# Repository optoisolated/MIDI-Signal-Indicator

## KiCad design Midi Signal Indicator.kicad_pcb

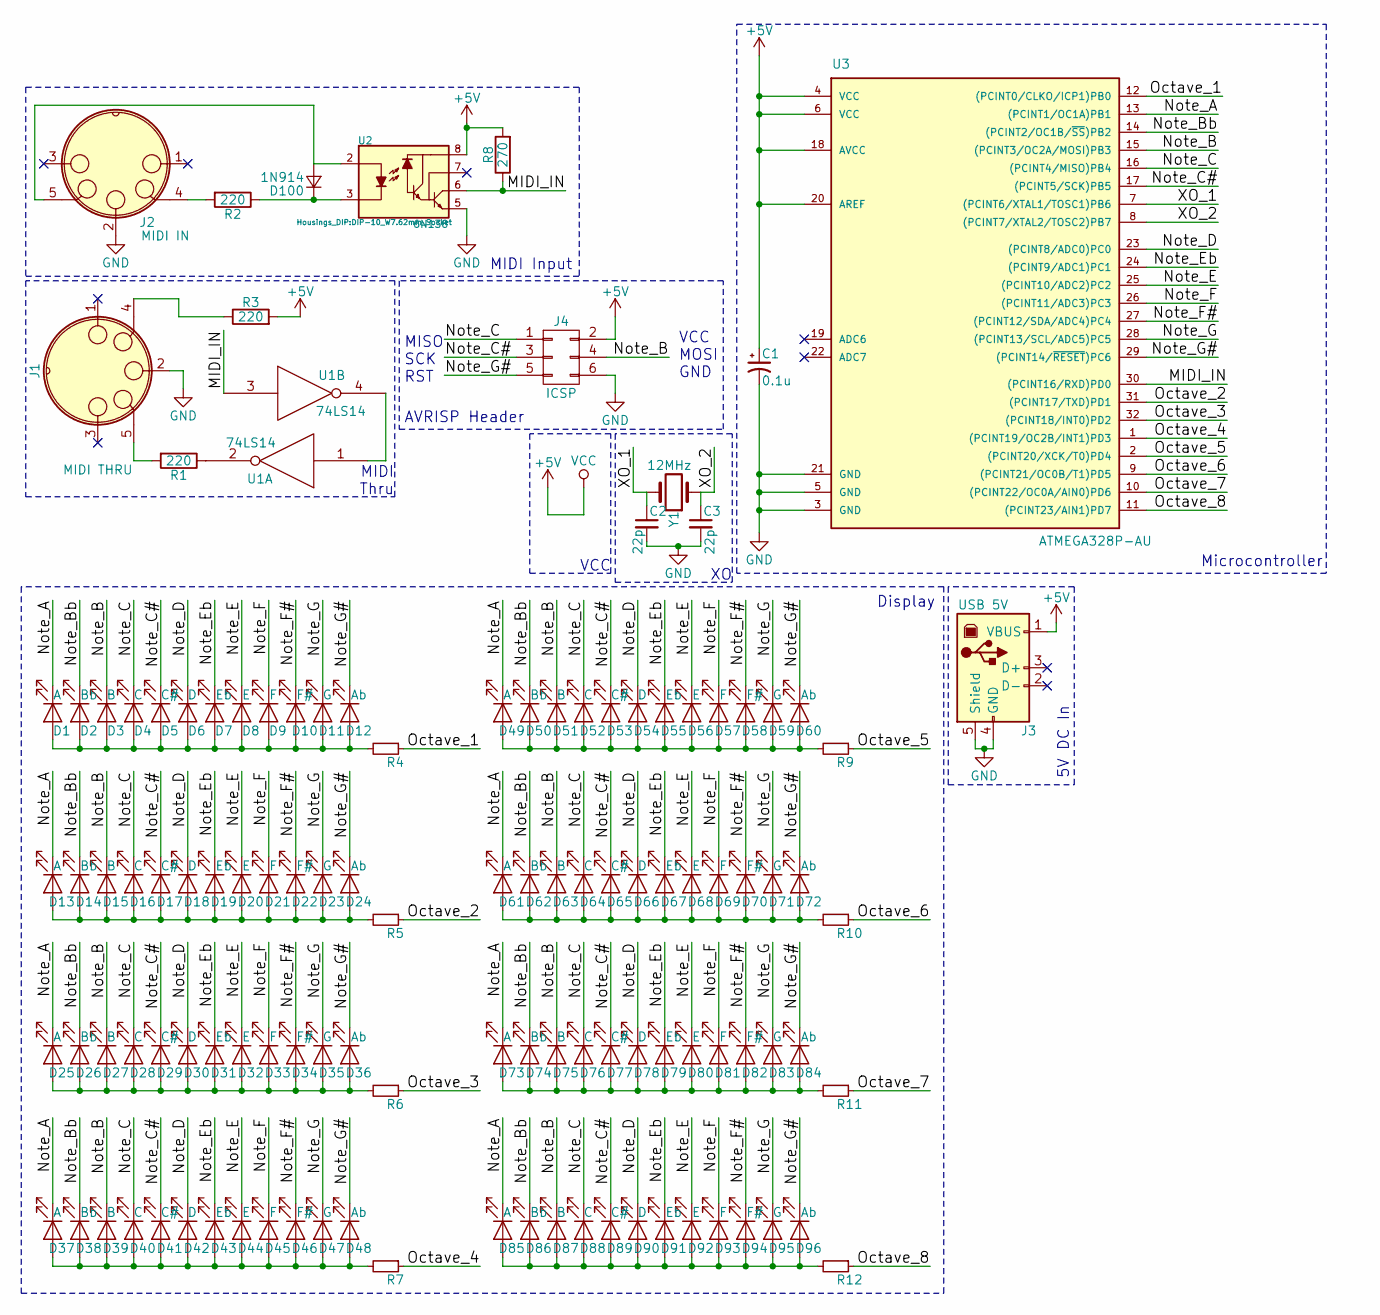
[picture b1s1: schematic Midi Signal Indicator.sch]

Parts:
C1: 0.1u; C_Disc_D5.0mm_W2.5mm_P2.50mm
C2, C3: 22p; C_Disc_D5.0mm_W2.5mm_P2.50mm
D1, D13, D25, D37, D49, D61, D73, D85: A; LED_1206
D2, D14, D26, D38, D50, D62, D74, D86: Bb; LED_1206
D3, D15, D27, D39, D51, D63, D75, D87: B; LED_1206
D4, D16, D28, D40, D52, D64, D76, D88: C; LED_1206
D5, D17, D29, D41, D53, D65, D77, D89: C#; LED_1206
D6, D18, D30, D42, D54, D66, D78, D90: D; LED_1206
D7, D19, D31, D43, D55, D67, D79, D91: Eb; LED_1206
D8, D20, D32, D44, D56, D68, D80, D92: E; LED_1206
D9, D21, D33, D45, D57, D69, D81, D93: F; LED_1206
D10, D22, D34, D46, D58, D70, D82, D94: F#; LED_1206
D11, D23, D35, D47, D59, D71, D83, D95: G; LED_1206
D12, D24, D36, D48, D60, D72, D84, D96: Ab; LED_1206
D100: 1N914; D_DO-15_P12.70mm_Horizontal
J1: MIDI THRU; SDS-50J
J2: MIDI IN; SDS-50J
J3: USB 5V; USB_B
J4: ICSP; Pin_Header_Straight_2x03_Pitch2.54mm
R1, R2, R3, R4, R5, R6, R7, R9, R10, R11, R12: 220; R_0603
R8: 270; R_0603
U1: 74LS14; DIP-14_W7.62mm_Socket
U2: 6N138; DIP-10_W7.62mm_Socket
U3: ATMEGA328P-AU; DIP-32_W7.62mm
Y1: 12MHz; Crystal_HC52-U_Vertical

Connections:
+5V: C1.1, J3.1 (VBUS), J4.2, R3.2, R8.2, U1.14 (VCC), U2.8, U3.4 (VCC), U3.6 (VCC), U3.18 (AVCC), U3.20 (AREF)
/MIDI_IN: R8.1, U1.3, U2.6, U3.30 ((PCINT16/RXD)PD0)
/Note_A: D1.1 (K), D13.1 (K), D25.1 (K), D37.1 (K), D49.1 (K), D61.1 (K), D73.1 (K), D85.1 (K), U3.13 ((PCINT1/OC1A)PB1)
/Note_B: D3.1 (K), D15.1 (K), D27.1 (K), D39.1 (K), D51.1 (K), D63.1 (K), D75.1 (K), D87.1 (K), J4.4, U3.15 ((PCINT3/OC2A/MOSI)PB3)
/Note_Bb: D2.1 (K), D14.1 (K), D26.1 (K), D38.1 (K), D50.1 (K), D62.1 (K), D74.1 (K), D86.1 (K), U3.14 ((PCINT2/OC1B/~SS~)PB2)
/Note_C: D4.1 (K), D16.1 (K), D28.1 (K), D40.1 (K), D52.1 (K), D64.1 (K), D76.1 (K), D88.1 (K), J4.1, U3.16 ((PCINT4/MISO)PB4)
/Note_C#: D5.1 (K), D17.1 (K), D29.1 (K), D41.1 (K), D53.1 (K), D65.1 (K), D77.1 (K), D89.1 (K), J4.3, U3.17 ((PCINT5/SCK)PB5)
/Note_D: D6.1 (K), D18.1 (K), D30.1 (K), D42.1 (K), D54.1 (K), D66.1 (K), D78.1 (K), D90.1 (K), U3.23 ((PCINT8/ADC0)PC0)
/Note_E: D8.1 (K), D20.1 (K), D32.1 (K), D44.1 (K), D56.1 (K), D68.1 (K), D80.1 (K), D92.1 (K), U3.25 ((PCINT10/ADC2)PC2)
/Note_Eb: D7.1 (K), D19.1 (K), D31.1 (K), D43.1 (K), D55.1 (K), D67.1 (K), D79.1 (K), D91.1 (K), U3.24 ((PCINT9/ADC1)PC1)
/Note_F: D9.1 (K), D21.1 (K), D33.1 (K), D45.1 (K), D57.1 (K), D69.1 (K), D81.1 (K), D93.1 (K), U3.26 ((PCINT11/ADC3)PC3)
/Note_F#: D10.1 (K), D22.1 (K), D34.1 (K), D46.1 (K), D58.1 (K), D70.1 (K), D82.1 (K), D94.1 (K), U3.27 ((PCINT12/SDA/ADC4)PC4)
/Note_G: D11.1 (K), D23.1 (K), D35.1 (K), D47.1 (K), D59.1 (K), D71.1 (K), D83.1 (K), D95.1 (K), U3.28 ((PCINT13/SCL/ADC5)PC5)
/Note_G#: D12.1 (K), D24.1 (K), D36.1 (K), D48.1 (K), D60.1 (K), D72.1 (K), D84.1 (K), D96.1 (K), J4.5, U3.29 ((PCINT14/~RESET~)PC6)
/Octave_1: R4.1, U3.12 ((PCINT0/CLKO/ICP1)PB0)
/Octave_2: R5.1, U3.31 ((PCINT17/TXD)PD1)
/Octave_3: R6.1, U3.32 ((PCINT18/INT0)PD2)
/Octave_4: R7.1, U3.1 ((PCINT19/OC2B/INT1)PD3)
/Octave_5: R9.1, U3.2 ((PCINT20/XCK/T0)PD4)
/Octave_6: R10.1, U3.9 ((PCINT21/OC0B/T1)PD5)
/Octave_7: R11.1, U3.10 ((PCINT22/OC0A/AIN0)PD6)
/Octave_8: R12.1, U3.11 ((PCINT23/AIN1)PD7)
/XO_1: C2.1, U3.7 ((PCINT6/XTAL1/TOSC1)PB6), Y1.2
/XO_2: C3.1, U3.8 ((PCINT7/XTAL2/TOSC2)PB7), Y1.1
GND: C1.2, C2.2, C3.2, J1.2, J2.2, J3.4 (GND), J3.5 (Shield), J4.6, U1.7 (GND), U2.5, U3.3 (GND), U3.5 (GND), U3.21 (GND)
unnamed: D1.2 (A), D2.2 (A), D3.2 (A), D4.2 (A), D5.2 (A), D6.2 (A), D7.2 (A), D8.2 (A), D9.2 (A), D10.2 (A), D11.2 (A), D12.2 (A), R4.2
unnamed: D13.2 (A), D14.2 (A), D15.2 (A), D16.2 (A), D17.2 (A), D18.2 (A), D19.2 (A), D20.2 (A), D21.2 (A), D22.2 (A), D23.2 (A), D24.2 (A), R5.2
unnamed: D25.2 (A), D26.2 (A), D27.2 (A), D28.2 (A), D29.2 (A), D30.2 (A), D31.2 (A), D32.2 (A), D33.2 (A), D34.2 (A), D35.2 (A), D36.2 (A), R6.2
unnamed: D37.2 (A), D38.2 (A), D39.2 (A), D40.2 (A), D41.2 (A), D42.2 (A), D43.2 (A), D44.2 (A), D45.2 (A), D46.2 (A), D47.2 (A), D48.2 (A), R7.2
unnamed: D49.2 (A), D50.2 (A), D51.2 (A), D52.2 (A), D53.2 (A), D54.2 (A), D55.2 (A), D56.2 (A), D57.2 (A), D58.2 (A), D59.2 (A), D60.2 (A), R9.2
unnamed: D61.2 (A), D62.2 (A), D63.2 (A), D64.2 (A), D65.2 (A), D66.2 (A), D67.2 (A), D68.2 (A), D69.2 (A), D70.2 (A), D71.2 (A), D72.2 (A), R10.2
unnamed: D73.2 (A), D74.2 (A), D75.2 (A), D76.2 (A), D77.2 (A), D78.2 (A), D79.2 (A), D80.2 (A), D81.2 (A), D82.2 (A), D83.2 (A), D84.2 (A), R11.2
unnamed: D85.2 (A), D86.2 (A), D87.2 (A), D88.2 (A), D89.2 (A), D90.2 (A), D91.2 (A), D92.2 (A), D93.2 (A), D94.2 (A), D95.2 (A), D96.2 (A), R12.2
unnamed: D100.1 (K), R2.1, U2.3
unnamed: D100.2 (A), J2.5, U2.2
unnamed: J1.4, R3.1
unnamed: J1.5, R1.2
unnamed: J2.4, R2.2
unnamed: R1.1, U1.2
unnamed: U1.1, U1.4

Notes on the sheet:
MIDI Input
MIDI Thru
Display
MISO SCK RST
VCC MOSI GND
AVRISP Header
Microcontroller
5V DC In
VCC

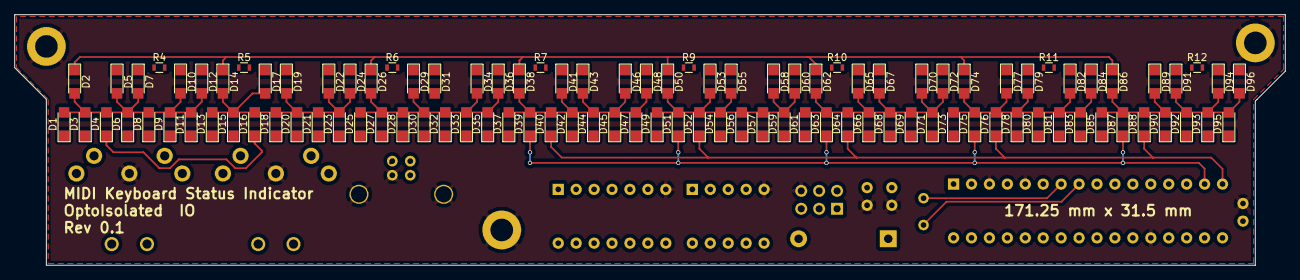
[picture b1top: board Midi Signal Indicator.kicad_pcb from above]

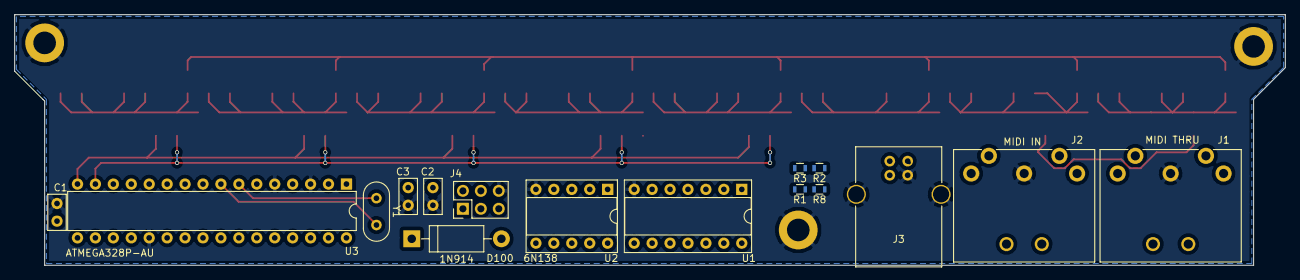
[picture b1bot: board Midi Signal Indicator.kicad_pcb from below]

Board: 2 copper layers, 180.0 x 35.5 mm, 120 parts (16 on the bottom side), 40 nets.
